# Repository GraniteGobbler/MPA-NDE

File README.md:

# MPA-NDE

This is a repository for lab work for the course MPA-NDE

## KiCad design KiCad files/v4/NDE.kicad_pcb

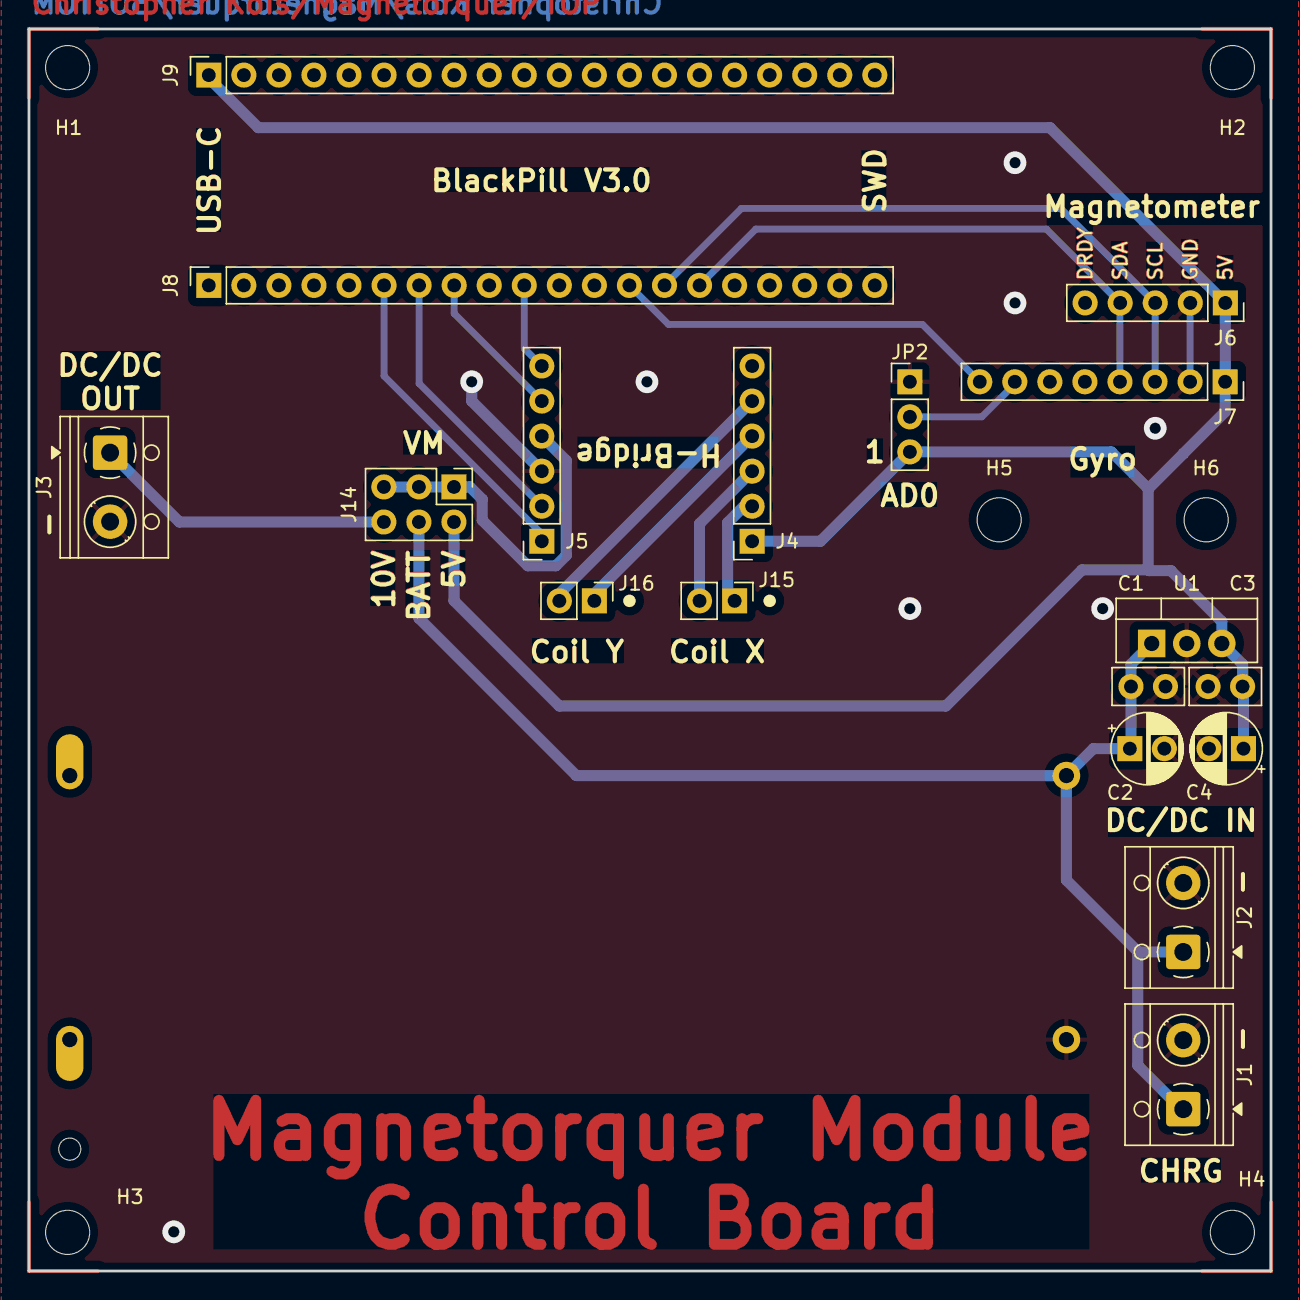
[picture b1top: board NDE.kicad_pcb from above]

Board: 2 copper layers, 90.0 x 90.0 mm, 25 parts (1 on the bottom side), 17 nets.

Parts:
BT1: 1049; BAT_1049
C1, C3: 100n; C_Disc_D5.0mm_W2.5mm_P2.50mm
C2, C4: 10u; CP_Radial_D5.0mm_P2.50mm
H1, H2, H3, H4, H5, H6: MountingHole; MountingHole_3.2mm_M3_ISO14580
J1: Nabíjací modul; TerminalBlock_RND_205-00012_1x02_P5.00mm_Horizontal
J2: Step-up input; TerminalBlock_RND_205-00012_1x02_P5.00mm_Horizontal
J3: Step-up output; TerminalBlock_RND_205-00012_1x02_P5.00mm_Horizontal
J4, J5: PinSocket_1x06_P2.54mm_Vertical
J6: Conn_01x05_Socket; PinSocket_1x05_P2.54mm_Vertical
J7: Conn_01x08_Socket; PinSocket_1x08_P2.54mm_Vertical
J8, J9: Conn_01x20_Socket; PinSocket_1x20_P2.54mm_Vertical
J14: VM_Select; PinHeader_2x03_P2.54mm_Vertical
J15, J16: Conn_01x02_Pin; PinHeader_1x02_P2.54mm_Vertical
JP2: Jumper_3_Open; PinHeader_1x03_P2.54mm_Vertical
U1: LM7805_TO220; TO-220-3_Vertical

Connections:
+5V: C3.1, C4.1, J4.1, J6.1, J7.1, J9.1, J14.2, JP2.3 (B), U1.3 (VO)
+10V: J3.1, J14.6
+BATT: BT1.P1, C1.1, C2.1, J1.1, J2.1, J14.4, U1.1 (VI)
/BlackPill V3.0/A9: J5.1, J8.6
/BlackPill V3.0/A10: J5.2, J8.7
/BlackPill V3.0/A11: J5.5, J8.8
/BlackPill V3.0/A15: J5.6, J8.10
/GY_INT: J7.8, J8.13
/Gyroskop/AD0: J7.7, JP2.2 (C)
/H-mostík/OUT1: J4.2, J15.1
/H-mostík/OUT2: J4.3, J15.2
/H-mostík/OUT3: J4.4, J16.1
/H-mostík/OUT4: J4.5, J16.2
/H-mostík/VCC: J5.4, J14.1, J14.3, J14.5
/SCL1: J6.3, J7.3, J8.14
/SDA1: J6.4, J7.4, J8.15
GND: BT1.N2, C1.2, C2.2, C3.2, C4.2, J1.2, J2.2, J3.2, J5.3, J6.2, J7.2, J8.19, JP2.1 (A), U1.2 (GND)

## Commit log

2025-02-20 Hello World test code
2025-03-06 Create folder
2025-03-06 Added SMT project
2025-03-08 Schematic layout
2025-03-08 Board v1
2025-03-08 Removed autosave
2025-03-09 File tree restructure
2025-03-09 Remove v2
2025-03-09 Modified layout
2025-03-10 Improved routing and layout
2025-03-10 v2 ready for manufacturing
2025-03-10 Generated Gerber files
2025-03-10 Modified text for top layer
2025-03-12 Added models
2025-03-12 Added ibom
2025-03-12 Removed backups
2025-03-12 Updated gitignore
2025-03-12 Board2Pdf generated file
2025-03-13 PCB2Blender export
2025-03-13 V3 modified track width, socket spacing, added 5V selector
2025-03-15 Modified module pin spacing, thickened traces
2025-03-16 gitignore update
2025-03-20 Added compass test
2025-03-21 Identified footprint issue - needs fixing
2025-03-22 Added cubesat frame models and assembly.
2025-03-26 Working first iteration of compass
2025-04-10 Updated gitignore settings, sync
2025-04-10 Added IMU library and basic data read
2025-04-10 Fixed merging issue with bad project settings.
2025-04-10 Added discokit pinout
2025-04-10 Added COIL_Y for GPIO
2025-04-17 Removed metadata edited gitignore
2025-04-17 Added images to a single folder
2025-04-18 Last class upload
2025-04-30 Added a non working to a new branch
2025-05-01 Massive progress, magnetometer and external field compensation is working
2025-05-05 Regenerated board .step file
2025-05-05 Regenerated board pdfs
2025-05-05 Regenerated .step file to contain tracks
2025-05-05 Added FBX
2025-05-05 Blender project commit
2025-05-05 Rendered images
2025-05-08 Edited render to have 3D-printed effect
2025-05-08 Transparent version
2025-05-08 Added image to the readme
2025-05-08 Edit
2025-05-08 Blender file save
2025-05-09 Updated schematic labeling
2025-05-09 Initial commit for v4
2025-05-09 Fixed unconnected GND of MCU and flipped H-bridge sockets
2025-05-09 Generated output files for docs. Removed old fabrication files.
2025-05-10 Modified to use DEG_TO_RAD
2025-05-10 Added newest fusion file
